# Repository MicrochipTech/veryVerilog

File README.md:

# veryVerilog

veryVerilog enables an easy way to program PICs from family 
- **PIC16F131xy**
- **PIC16F132xy**
- **PIC16F180xy**
- **PIC18FxyQ35**

over a Web Browser without the need to install any software using a PIC as a USB HiD device. 

The project is based on 3 parts:
- USB-HID PCB (hardware)
- USB-HID Hex File (firmware)
- Web Page to flash Hex files a PIC device attached to the hardware

The PCB looks like this and is based on a [**PIC16F1455**](https://www.microchip.com/en-us/product/pic16f1455) .

The [**PIC16F1455**](https://www.microchip.com/en-us/product/pic16f1455) needs a [**custom firmware**](/firmware/hex/U1_PIC16F1455_v1.20.hex) to perform as ICSP programmer.

The IC on the left-hand side is the [**PIC16F1455**](https://www.microchip.com/en-us/product/pic16f1455)-I/P and IC on the right-hand side is the miniFPGA ([**PIC16F13145**](https://www.microchip.com/en-us/product/pic16f13145)-I/P) to be programmed.

# Program a PIC in 4 Steps

It is that easy:

## 1. Insert the Hardware

Plug the miniFPGA dongle in your computer.

## 2. Click the Web Page

Open the Web Page: [https://microchiptech.github.io/veryVerilog](https://microchiptech.github.io/veryVerilog/).

You will see the veryVerilog Web Page:

## 3. Connect to Programmer

Click the button "Connect to Programmer" and select the miniFPGA device:

If you have multiple programmers connected, click "identify Programmer" and the LEDs of the connected board will blink for about 2 seconds.

The device is recognized and the Web Page displays information about the connected PIC and the identification of the program already flashed on the device (User Id)

## 4. Drag and Drop

Drag a HEX file on the *"Drag and Drop"* area and the program will be transfered automatically to the PIC.

Alternatively, you can click the **"Browse for HEX file"** button to select a HEX file from your file system. This is particularly useful when working with IDEs where you can copy and paste file paths.

Have fun!

## Additional Features

### Reset Target Device

After connecting to the programmer, a **"Reset Target"** button becomes available. Clicking this button will reset the target PIC.

### Device Detection

When you connect to a programmer:
- If the device is **recognized**, the web page displays the PIC model name (e.g., "PIC16F13145") and its User ID
- If the device is **not recognized** or reads an invalid ID (like 0x0000), the page will display: **"Unknown PIC with DEVID 0x[hex_value]"** along with the actual device ID that was read

This helps in debugging connectivity issues or identifying when an unsupported PIC is connected.

**Tip:** Click on the **UserId** display to open a detailed information window showing:
- **MCU Parameters** - Device ID, Revision ID, Memory sizes (ERSIZ, WLSIZ, URSIZ, EESIZ), Program Counter size (PCNT), and other device-specific information
- **Programmer Parameters** - Hardware UART baud rate and other programmer settings

### Reading Memory Regions

After connecting to the programmer, you can read the entire contents of the target PIC device:

1. Click the **Settings** dropdown (split button next to "Identify Programmer")
2. Select **"Read Device"** from the menu
3. The device memory will be read and automatically displayed in a modal window

The memory viewer organizes data into collapsible sections:
- **Program Flash** - The main program memory (displayed in rows of 16 words)
- **EEPROM** - Data EEPROM memory (if available on the device, displayed in rows of 8 bytes)
- **UserId** - User ID locations (displayed in rows of 4 words)
- **Config Words** - Configuration bits

You can also access previously read memory using the **"Show Memory"** option without reading the device again. This is useful for comparing data or reviewing what was last read from the device.

### Programming Settings

The **Settings** dropdown provides options to customize which memory regions are programmed and whether verification is performed:

**Default Behavior:**
- All memory regions are programmed: **Program** (Flash), **EEPROM**, **UserId**, and **Config Bits**
- After programming, the code is automatically **verified** to ensure it was written correctly

**Customizing Memory Regions:**

Click the **Settings** dropdown to access programming options. You can selectively choose which memory regions to program by checking/unchecking:
- **Program** - Main program flash memory
- **EEPROM** - Data EEPROM memory (if available on the device)
- **UserId** - User ID locations
- **Config Bits** - Configuration bits

**Verification:**
- The **Verify** option (enabled by default) checks that the programmed memory matches the expected values
- This ensures programming integrity but may increase programming time slightly
- You can disable verification if faster programming is needed, though this is not recommended

### Serial Terminal

The veryVerilog web page includes a built-in **Serial Terminal** for communicating directly with the target PIC over a serial (UART) connection.

#### Opening the Serial Terminal

Click the **"Serial Terminal"** tab to open the terminal window:

#### Connecting to a Serial Port

Click the **"Connect"** button and a browser popup will appear listing the available serial ports on your computer. Select the desired port (e.g., the miniFPGA board) and click **Connect**:

Once connected, the status indicator turns green and the terminal displays a confirmation message with a timestamp:

#### Sending Data

Type a command in the input field at the bottom of the terminal and press **Enter** or click the **"Send"** button. Use the **line ending** dropdown (default: **CR+LF**) to choose the line termination characters appended to each message.

#### Terminal Controls

The toolbar at the top of the terminal provides the following controls:

| Button | Description |
|--------|-------------|
| **Connect** / **Disconnect** | Connect to or disconnect from a serial port. The button label changes depending on the connection state. |
| **Pause** | Pause the terminal output. Incoming data is still received but the display stops scrolling. Click again to resume. |
| **Graph** | Open a graphing view to plot numeric data received from the serial port in real time (see [Graph Mode](#graph-mode) below). |
| **X** (Clear Terminal) | Clear all text currently displayed in the terminal window. |
| **Hide Terminal** | Collapse the serial terminal panel to free up screen space. Click the **"Serial Terminal"** tab again to reopen it. |

#### Graph Mode

Click the **"Graph"** button to switch the terminal into a real-time plotting view. The graph plots numeric data received over the serial port in **CSV format** — each line of text represents one data point in time, with comma-separated values mapping to individual channels.

**Expected data format:**

The PIC should send an optional **header line** followed by **numeric data lines**, all in CSV format terminated by a newline:

```
header1,header2,header3\n   ← optional: names for each channel
value1,value2,value3\n      ← numeric data (one sample per line)
value1,value2,value3\n
...
```

The first non-numeric line received is used as the **channel names** displayed in the graph legend. If no header is sent, channels are automatically named `Ch1`, `Ch2`, etc.

> **Tip:** Always send a header line at PIC startup to get meaningful trace names. Without it, UART noise or partial bytes at connection time may produce garbled labels.

**Example — single channel** (e.g., ADC reading):
```
ADC
512
523
531
548
```

**Example — multiple channels** (e.g., temperature and humidity sensors):
```
Temperature,Humidity
23.5,65.2
23.6,64.8
23.7,65.0
23.8,64.5
```

**Example C code** to send plottable data from a PIC:
```c
// Send header once at startup
printf("ADC,Temperature\r\n");

// Then send data periodically
while (1) {
    printf("%d,%d\r\n", adc_value, temperature);
    __delay_ms(100);
}
```

Each comma-separated value is plotted as a separate trace on the graph, allowing you to monitor multiple signals simultaneously. The example below shows two channels — one counting up from 0 to 10 and the other counting down from 10 to 0 — plotted in real time:

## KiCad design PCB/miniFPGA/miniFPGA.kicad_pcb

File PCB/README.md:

# v3.0 PCB Readme

## Overview
This document provides essential information regarding the v3.0 PCB (Printed Circuit Board) design, including features, specifications, and usage instructions.

## Features
- **Compact Design**: The v3.0 PCB is designed to be space-efficient while maintaining functionality.
- **Power Management**: Improved power distribution for optimal performance and reduced heat generation.

## Specifications
- **Dimensions**: 57.4mm x 24.89mm
- **Layer Count**: 2 layers
- **Material**: FR-4
- **Operating Voltage**: 5V (from USB A)
- **Current Rating**: 100mA without external application

## Schematic
Refer to the attached schematic diagram for detailed connections and component placements.

## Assembly Instructions
1. **Component Placement**: Follow the provided schematic for correct component placement. Use IBOM from miniFPGA/bom/miniFPGA?ibom.html
2. **Soldering**: Use appropriate soldering techniques to ensure reliable connections.
3. **Testing**: After assembly, U2 LEDs will shor a running light effect.

## Usage
- Connect the PCB USB-A port. Use the [web programmer application](https://microchiptech.github.io/veryVerilog)
- The lectures are on [Microchip try platform](https://try.microchip.com/training/logic-circuit-design-101)     

## Troubleshooting
- **No Power**: Check power supply connections and ensure the correct voltage is applied.
- **Component Failure**: Inspect for soldering issues or damaged components.

## License
This project is licensed under the MIT License - see the LICENSE file for details.

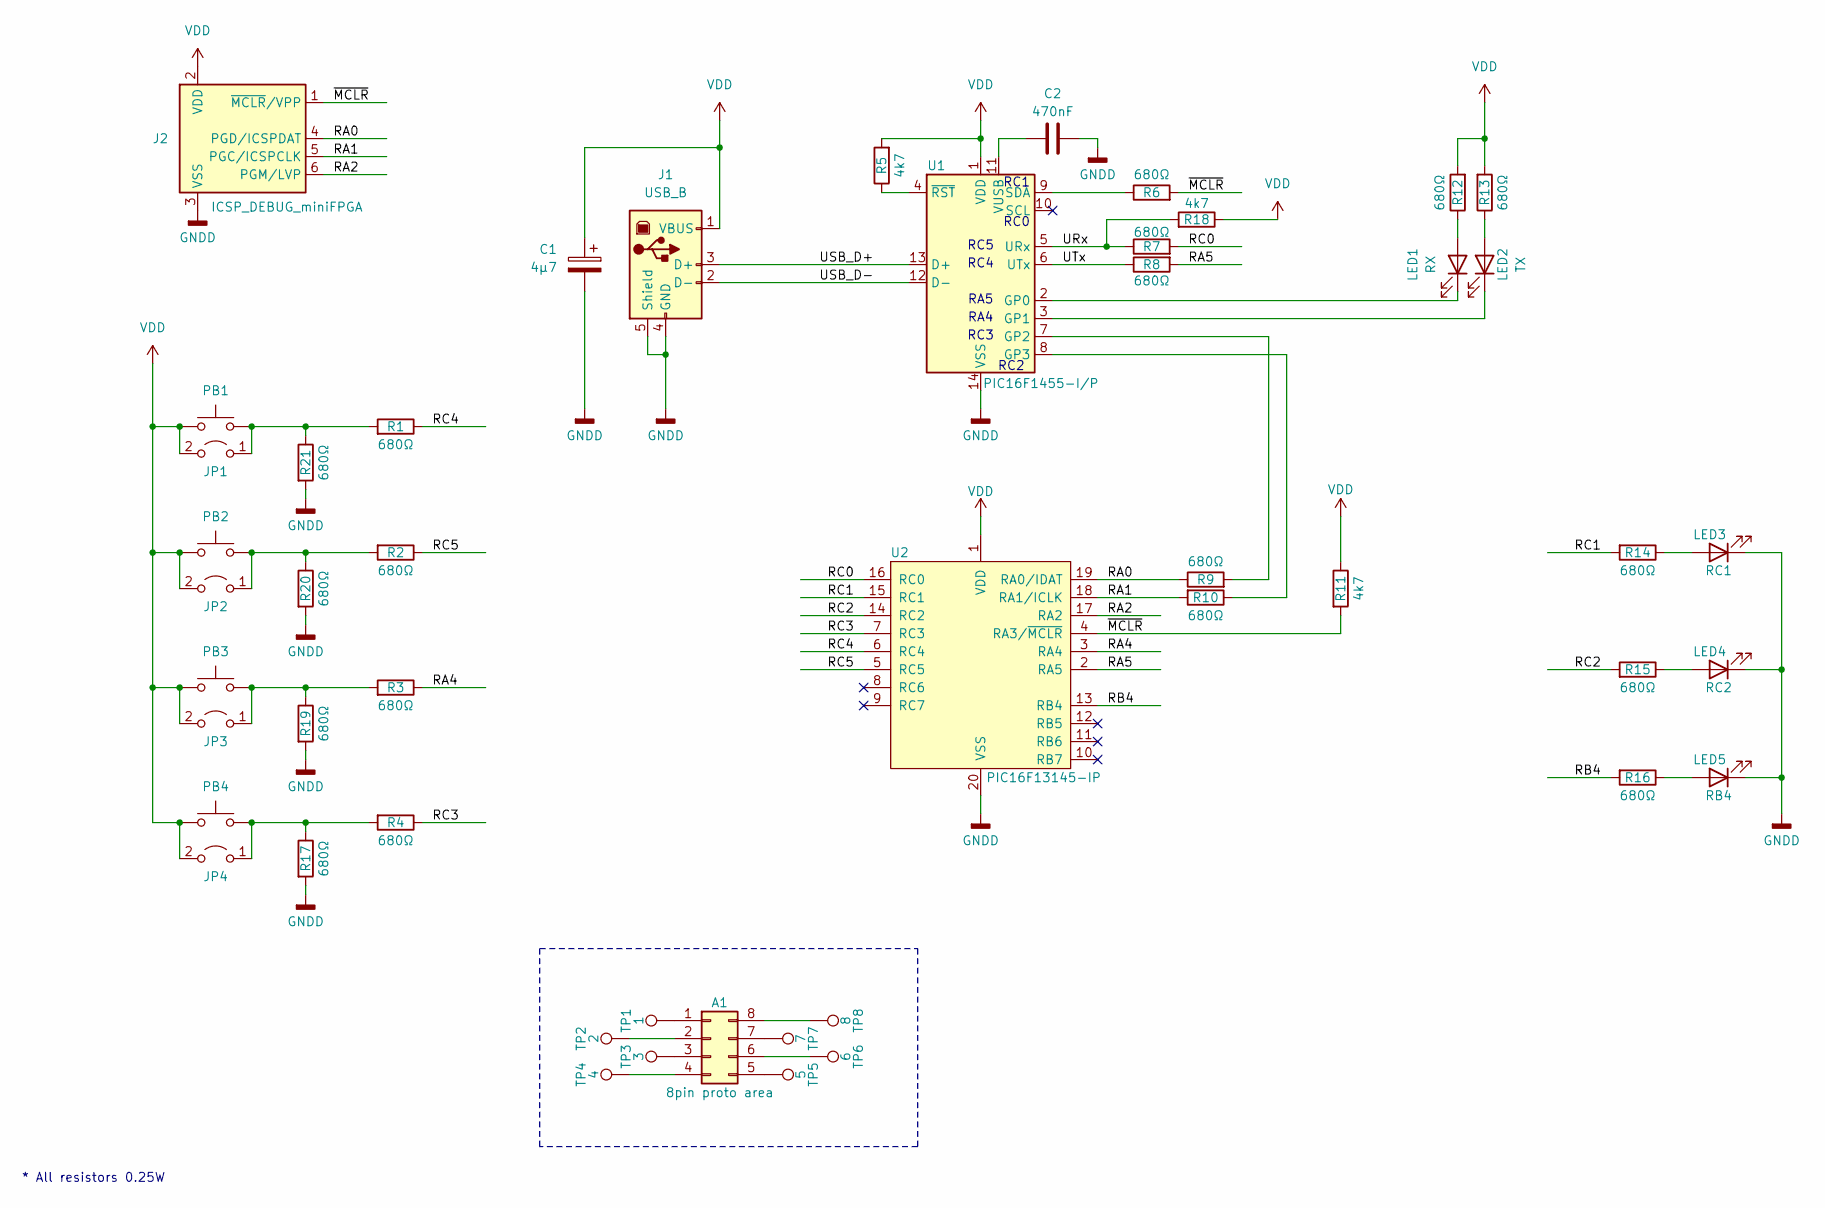
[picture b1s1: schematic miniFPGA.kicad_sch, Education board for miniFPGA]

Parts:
A1: 8pin proto area; 8pin_proto
C1: 4µ7; CP_Radial_D4.0mm_P2.00mm
C2: 470nF; C_Rect_L4.6mm_W2.0mm_P2.50mm_MKS02_FKP02
J1: USB_B; USB_A_CNCTech_1001-011-01101_Horizontal
J2: ICSP_DEBUG_miniFPGA; PinHeader_1x06_P2.54mm_Horizontal
JP1: RC4; PinHeader_1x02_P2.54mm_Vertical
JP2: RC5; PinHeader_1x02_P2.54mm_Vertical
JP3: RA4; PinHeader_1x02_P2.54mm_Vertical
JP4: RC3; PinHeader_1x02_P2.54mm_Vertical
LED1: RX; LED_D3.0mm
LED2: TX; LED_D3.0mm
LED3: RC1; LED_D3.0mm
LED4: RC2; LED_D3.0mm
LED5: RB4; LED_D3.0mm
PB1: RC4; SW_PUSH_6mm_H5mm
PB2: RC5; SW_PUSH_6mm_H5mm
PB3: RA4; SW_PUSH_6mm_H5mm
PB4: RC3; SW_PUSH_6mm_H5mm
R1, R2, R3, R4, R6, R7, R8, R9, R10, R12, R13, R14, R15, R16, R17, R19, R20, R21: 680Ω; R_Axial_L3.6mm_D1.6mm_P1.90mm_Vertical
R5, R11, R18: 4k7; R_Axial_DIN0204_L3.6mm_D1.6mm_P5.08mm_Horizontal
TP1: 1; TestPoint_Pad_1.5x1.5mm
TP2: 2; TestPoint_Pad_D1.5mm
TP3: 3; TestPoint_Pad_D1.5mm
TP4: 4; TestPoint_Pad_D1.5mm
TP5: 5; TestPoint_Pad_D1.5mm
TP6: 6; TestPoint_Pad_D1.5mm
TP7: 7; TestPoint_Pad_D1.5mm
TP8: 8; TestPoint_Pad_D1.5mm
U1: PIC16F1455-I/P; DIP-14_W7.62mm
U2: PIC16F13145-IP; DIP-20_W7.62mm

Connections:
/RA0: J2.4 (PGD/ICSPDAT), R9.1, U2.19 (RA0/IDAT)
/RA1: J2.5 (PGC/ICSPCLK), R10.2, U2.18 (RA1/ICLK)
/RA2: J2.6 (PGM/LVP), U2.17 (RA2)
/RA4: R3.1, U2.3 (RA4)
/RA5: R8.2, U2.2 (RA5)
/RB4: R16.2, U2.13 (RB4)
/RC0: R7.2, U2.16 (RC0)
/RC1: R14.2, U2.15 (RC1)
/RC2: R15.2, U2.14 (RC2)
/RC3: R4.1, U2.7 (RC3)
/RC4: R1.1, U2.6 (RC4)
/RC5: R2.1, U2.5 (RC5)
/URx: R7.1, R18.2, U1.5 (URx)
/USB_D+: J1.3 (D+), U1.13 (D+)
/USB_D-: J1.2 (D-), U1.12 (D-)
/UTx: R8.1, U1.6 (UTx)
/~MCLR: J2.1 (~MCLR/VPP), R6.2, R11.2, U2.4 (RA3/~MCLR)
GNDD: C1.2, C2.2, J1.4 (GND), J1.5 (Shield), J2.3 (VSS), LED3.1 (K), LED4.1 (K), LED5.1 (K), R17.2, R19.2, R20.2, R21.2, U1.14 (VSS), U2.20 (VSS)
unnamed: A1.1, TP1.1
unnamed: A1.2, TP2.1
unnamed: A1.3, TP3.1
unnamed: A1.4, TP4.1
unnamed: A1.5, TP5.1
unnamed: A1.6, TP6.1
unnamed: A1.7, TP7.1
unnamed: A1.8, TP8.1
unnamed: JP1.1 (A), PB1.1, R1.2, R21.1
unnamed: JP2.1 (A), PB2.1, R2.2, R20.1
unnamed: JP3.1 (A), PB3.1, R3.2, R19.1
unnamed: JP4.1 (A), PB4.1, R4.2, R17.1
unnamed: LED1.2 (A), R12.1
unnamed: LED1.1 (K), U1.2 (GP0)
unnamed: LED2.2 (A), R13.1
unnamed: LED2.1 (K), U1.3 (GP1)
unnamed: LED3.2 (A), R14.1
unnamed: LED4.2 (A), R15.1
unnamed: LED5.2 (A), R16.1
unnamed: R9.2, U1.7 (GP2)
unnamed: R10.1, U1.8 (GP3)
unnamed: R6.1, U1.9 (SDA)
unnamed: C2.1, U1.11 (VUSB)
unnamed: R5.1, U1.4 (~RST)
VDD: C1.1, J1.1 (VBUS), J2.2 (VDD), JP1.2 (B), JP2.2 (B), JP3.2 (B), JP4.2 (B), PB1.2, PB2.2, PB3.2, PB4.2, R5.2, R11.1, R12.2, R13.2, R18.1, U1.1 (VDD), U2.1 (VDD)

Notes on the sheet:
RC3
RC1
RC0
RA5
RC4
RA4
* All resistors 0.25W
RC2
RC5

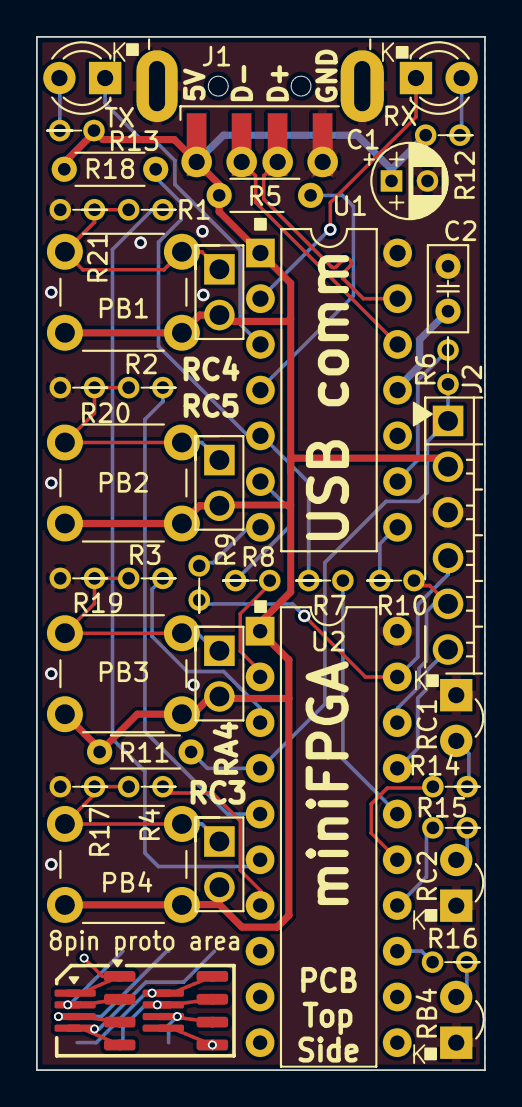
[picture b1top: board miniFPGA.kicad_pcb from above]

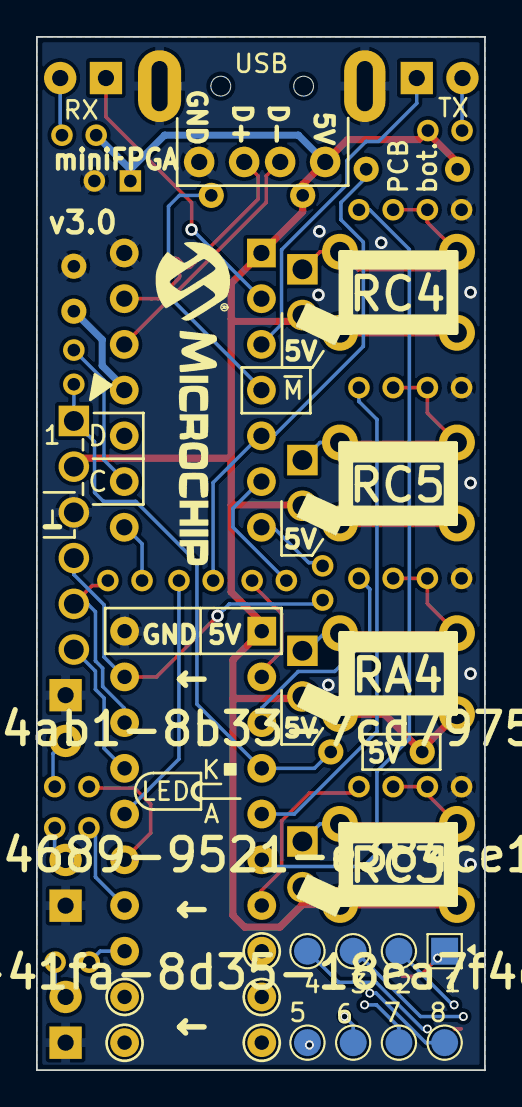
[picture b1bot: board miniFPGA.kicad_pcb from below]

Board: 2 copper layers, 24.9 x 57.4 mm, 49 parts (8 on the bottom side), 43 nets.

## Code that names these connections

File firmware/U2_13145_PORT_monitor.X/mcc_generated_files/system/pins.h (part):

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// get/set IO_RA0 aliases
#define IO_RA0_TRIS                 TRISAbits.TRISA0
#define IO_RA0_LAT                  LATAbits.LATA0
#define IO_RA0_PORT                 PORTAbits.RA0
#define IO_RA0_WPU                  WPUAbits.WPUA0
#define IO_RA0_OD                   ODCONAbits.ODCA0
#define IO_RA0_ANS                  ANSELAbits.ANSA0
#define IO_RA0_SetHigh()            do { LATAbits.LATA0 = 1; } while(0)
#define IO_RA0_SetLow()             do { LATAbits.LATA0 = 0; } while(0)
#define IO_RA0_Toggle()             do { LATAbits.LATA0 = ~LATAbits.LATA0; } while(0)
#define IO_RA0_GetValue()           PORTAbits.RA0
#define IO_RA0_SetDigitalInput()    do { TRISAbits.TRISA0 = 1; } while(0)
#define IO_RA0_SetDigitalOutput()   do { TRISAbits.TRISA0 = 0; } while(0)
#define IO_RA0_SetPullup()          do { WPUAbits.WPUA0 = 1; } while(0)
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// get/set IO_RA1 aliases
#define IO_RA1_TRIS                 TRISAbits.TRISA1
#define IO_RA1_LAT                  LATAbits.LATA1
#define IO_RA1_PORT                 PORTAbits.RA1
#define IO_RA1_WPU                  WPUAbits.WPUA1
#define IO_RA1_OD                   ODCONAbits.ODCA1
#define IO_RA1_ANS                  ANSELAbits.ANSA1
#define IO_RA1_SetHigh()            do { LATAbits.LATA1 = 1; } while(0)
#define IO_RA1_SetLow()             do { LATAbits.LATA1 = 0; } while(0)
#define IO_RA1_Toggle()             do { LATAbits.LATA1 = ~LATAbits.LATA1; } while(0)
#define IO_RA1_GetValue()           PORTAbits.RA1
#define IO_RA1_SetDigitalInput()    do { TRISAbits.TRISA1 = 1; } while(0)
#define IO_RA1_SetDigitalOutput()   do { TRISAbits.TRISA1 = 0; } while(0)
#define IO_RA1_SetPullup()          do { WPUAbits.WPUA1 = 1; } while(0)
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// get/set IO_RA2 aliases
#define IO_RA2_TRIS                 TRISAbits.TRISA2
#define IO_RA2_LAT                  LATAbits.LATA2
#define IO_RA2_PORT                 PORTAbits.RA2
#define IO_RA2_WPU                  WPUAbits.WPUA2
#define IO_RA2_OD                   ODCONAbits.ODCA2
#define IO_RA2_ANS                  ANSELAbits.ANSA2
#define IO_RA2_SetHigh()            do { LATAbits.LATA2 = 1; } while(0)
#define IO_RA2_SetLow()             do { LATAbits.LATA2 = 0; } while(0)
#define IO_RA2_Toggle()             do { LATAbits.LATA2 = ~LATAbits.LATA2; } while(0)
#define IO_RA2_GetValue()           PORTAbits.RA2
#define IO_RA2_SetDigitalInput()    do { TRISAbits.TRISA2 = 1; } while(0)
#define IO_RA2_SetDigitalOutput()   do { TRISAbits.TRISA2 = 0; } while(0)
#define IO_RA2_SetPullup()          do { WPUAbits.WPUA2 = 1; } while(0)
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// get/set IO_RA4 aliases
#define IO_RA4_TRIS                 TRISAbits.TRISA4
#define IO_RA4_LAT                  LATAbits.LATA4
#define IO_RA4_PORT                 PORTAbits.RA4
#define IO_RA4_WPU                  WPUAbits.WPUA4
#define IO_RA4_OD                   ODCONAbits.ODCA4
#define IO_RA4_ANS                  ANSELAbits.ANSA4
#define IO_RA4_SetHigh()            do { LATAbits.LATA4 = 1; } while(0)
#define IO_RA4_SetLow()             do { LATAbits.LATA4 = 0; } while(0)
#define IO_RA4_Toggle()             do { LATAbits.LATA4 = ~LATAbits.LATA4; } while(0)
#define IO_RA4_GetValue()           PORTAbits.RA4
#define IO_RA4_SetDigitalInput()    do { TRISAbits.TRISA4 = 1; } while(0)
#define IO_RA4_SetDigitalOutput()   do { TRISAbits.TRISA4 = 0; } while(0)
#define IO_RA4_SetPullup()          do { WPUAbits.WPUA4 = 1; } while(0)
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// get/set IO_RA5 aliases
#define IO_RA5_TRIS                 TRISAbits.TRISA5
#define IO_RA5_LAT                  LATAbits.LATA5
#define IO_RA5_PORT                 PORTAbits.RA5
#define IO_RA5_WPU                  WPUAbits.WPUA5
#define IO_RA5_OD                   ODCONAbits.ODCA5
#define IO_RA5_ANS                  ANSELAbits.ANSA5
#define IO_RA5_SetHigh()            do { LATAbits.LATA5 = 1; } while(0)
#define IO_RA5_SetLow()             do { LATAbits.LATA5 = 0; } while(0)
#define IO_RA5_Toggle()             do { LATAbits.LATA5 = ~LATAbits.LATA5; } while(0)
#define IO_RA5_GetValue()           PORTAbits.RA5
#define IO_RA5_SetDigitalInput()    do { TRISAbits.TRISA5 = 1; } while(0)
#define IO_RA5_SetDigitalOutput()   do { TRISAbits.TRISA5 = 0; } while(0)
#define IO_RA5_SetPullup()          do { WPUAbits.WPUA5 = 1; } while(0)
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// get/set IO_RB4 aliases
#define IO_RB4_TRIS                 TRISBbits.TRISB4
#define IO_RB4_LAT                  LATBbits.LATB4
#define IO_RB4_PORT                 PORTBbits.RB4
#define IO_RB4_WPU                  WPUBbits.WPUB4
#define IO_RB4_OD                   ODCONBbits.ODCB4
#define IO_RB4_ANS                  ANSELBbits.ANSB4
#define IO_RB4_SetHigh()            do { LATBbits.LATB4 = 1; } while(0)
#define IO_RB4_SetLow()             do { LATBbits.LATB4 = 0; } while(0)
#define IO_RB4_Toggle()             do { LATBbits.LATB4 = ~LATBbits.LATB4; } while(0)
#define IO_RB4_GetValue()           PORTBbits.RB4
#define IO_RB4_SetDigitalInput()    do { TRISBbits.TRISB4 = 1; } while(0)
#define IO_RB4_SetDigitalOutput()   do { TRISBbits.TRISB4 = 0; } while(0)
#define IO_RB4_SetPullup()          do { WPUBbits.WPUB4 = 1; } while(0)
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// get/set IO_RC0 aliases
#define IO_RC0_TRIS                 TRISCbits.TRISC0
#define IO_RC0_LAT                  LATCbits.LATC0
#define IO_RC0_PORT                 PORTCbits.RC0
#define IO_RC0_WPU                  WPUCbits.WPUC0
#define IO_RC0_OD                   ODCONCbits.ODCC0
#define IO_RC0_ANS                  ANSELCbits.ANSC0
#define IO_RC0_SetHigh()            do { LATCbits.LATC0 = 1; } while(0)
#define IO_RC0_SetLow()             do { LATCbits.LATC0 = 0; } while(0)
#define IO_RC0_Toggle()             do { LATCbits.LATC0 = ~LATCbits.LATC0; } while(0)
#define IO_RC0_GetValue()           PORTCbits.RC0
#define IO_RC0_SetDigitalInput()    do { TRISCbits.TRISC0 = 1; } while(0)
#define IO_RC0_SetDigitalOutput()   do { TRISCbits.TRISC0 = 0; } while(0)
#define IO_RC0_SetPullup()          do { WPUCbits.WPUC0 = 1; } while(0)
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// get/set IO_RC1 aliases
#define IO_RC1_TRIS                 TRISCbits.TRISC1
#define IO_RC1_LAT                  LATCbits.LATC1
#define IO_RC1_PORT                 PORTCbits.RC1
#define IO_RC1_WPU                  WPUCbits.WPUC1
#define IO_RC1_OD                   ODCONCbits.ODCC1
#define IO_RC1_ANS                  ANSELCbits.ANSC1
#define IO_RC1_SetHigh()            do { LATCbits.LATC1 = 1; } while(0)
#define IO_RC1_SetLow()             do { LATCbits.LATC1 = 0; } while(0)
#define IO_RC1_Toggle()             do { LATCbits.LATC1 = ~LATCbits.LATC1; } while(0)
#define IO_RC1_GetValue()           PORTCbits.RC1
#define IO_RC1_SetDigitalInput()    do { TRISCbits.TRISC1 = 1; } while(0)
#define IO_RC1_SetDigitalOutput()   do { TRISCbits.TRISC1 = 0; } while(0)
#define IO_RC1_SetPullup()          do { WPUCbits.WPUC1 = 1; } while(0)
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// get/set IO_RC2 aliases
#define IO_RC2_TRIS                 TRISCbits.TRISC2
#define IO_RC2_LAT                  LATCbits.LATC2
#define IO_RC2_PORT                 PORTCbits.RC2
#define IO_RC2_WPU                  WPUCbits.WPUC2
#define IO_RC2_OD                   ODCONCbits.ODCC2
#define IO_RC2_ANS                  ANSELCbits.ANSC2
#define IO_RC2_SetHigh()            do { LATCbits.LATC2 = 1; } while(0)
#define IO_RC2_SetLow()             do { LATCbits.LATC2 = 0; } while(0)
#define IO_RC2_Toggle()             do { LATCbits.LATC2 = ~LATCbits.LATC2; } while(0)
#define IO_RC2_GetValue()           PORTCbits.RC2
#define IO_RC2_SetDigitalInput()    do { TRISCbits.TRISC2 = 1; } while(0)
#define IO_RC2_SetDigitalOutput()   do { TRISCbits.TRISC2 = 0; } while(0)
#define IO_RC2_SetPullup()          do { WPUCbits.WPUC2 = 1; } while(0)
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// get/set IO_RC3 aliases
#define IO_RC3_TRIS                 TRISCbits.TRISC3
#define IO_RC3_LAT                  LATCbits.LATC3
#define IO_RC3_PORT                 PORTCbits.RC3
#define IO_RC3_WPU                  WPUCbits.WPUC3
#define IO_RC3_OD                   ODCONCbits.ODCC3
#define IO_RC3_ANS                  ANSELCbits.ANSC3
#define IO_RC3_SetHigh()            do { LATCbits.LATC3 = 1; } while(0)
#define IO_RC3_SetLow()             do { LATCbits.LATC3 = 0; } while(0)
#define IO_RC3_Toggle()             do { LATCbits.LATC3 = ~LATCbits.LATC3; } while(0)
#define IO_RC3_GetValue()           PORTCbits.RC3
#define IO_RC3_SetDigitalInput()    do { TRISCbits.TRISC3 = 1; } while(0)
#define IO_RC3_SetDigitalOutput()   do { TRISCbits.TRISC3 = 0; } while(0)
#define IO_RC3_SetPullup()          do { WPUCbits.WPUC3 = 1; } while(0)
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// get/set IO_RC4 aliases
#define IO_RC4_TRIS                 TRISCbits.TRISC4
#define IO_RC4_LAT                  LATCbits.LATC4
#define IO_RC4_PORT                 PORTCbits.RC4
#define IO_RC4_WPU                  WPUCbits.WPUC4
#define IO_RC4_OD                   ODCONCbits.ODCC4
#define IO_RC4_ANS                  ANSELCbits.ANSC4
#define IO_RC4_SetHigh()            do { LATCbits.LATC4 = 1; } while(0)
#define IO_RC4_SetLow()             do { LATCbits.LATC4 = 0; } while(0)
#define IO_RC4_Toggle()             do { LATCbits.LATC4 = ~LATCbits.LATC4; } while(0)
#define IO_RC4_GetValue()           PORTCbits.RC4
#define IO_RC4_SetDigitalInput()    do { TRISCbits.TRISC4 = 1; } while(0)
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
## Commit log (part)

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2024-12-17 update gitignore
2024-12-17 adding files
2024-12-17 enhancing readme
2024-12-17 update images
2024-12-17 adding gh-pages
2024-12-17 Feat include files (#1)
    * update gitignore
    * adding files
    * enhancing readme
    * adding gh-pages
    ---------
2024-12-17 adding github action
2024-12-17 saving files to gh-pages
2024-12-17 git commit -m "Add .nojekyll to disable Jekyll processing"
2024-12-17 update web page link
2024-12-17 exit LVP before disconnect
2024-12-17 adapted read and show memory
2024-12-17 including LVPExit where it was missing
2024-12-17 including verify
2024-12-18 including tooltips
2024-12-18 included variable verify. It is checked but not yet implemented
2024-12-18 Feat enhance web interface (#2)
    * exit LVP before disconnect
    * adapted read and show memory
    * including verify memory variable
    * including tooltips
    ---------
2024-12-18 Deploy www folder to gh-pages
2024-12-18 PCB v3 image, more details in readme
2024-12-18 lessons' placeholders are now hidden
2024-12-19 lessons' placeholders are now hidden (#11)
2024-12-19 sync to gh-pages
2024-12-19 hide lesson image from readme
2024-12-19 update firmware hex version
2024-12-19 update MPLabX U1 and U2 projects
2024-12-19 instruction to deploy gh-pages
2024-12-19 Fix u1 and u2 firmware missing (#12)
    * update firmware hex version
    * update MPLabX U1 and U2 projects
    * hide lesson image from readme
    * instruction to deploy gh-pages
    ---------
2024-12-19 PCB v3 image, more details in readme (#10)
    * PCB v3 image, more details in readme
    * Update README.md
    ---------
2025-01-02 fix handling no EEPROM
2025-01-02 fix handling no EEPROM (#18)
2025-01-02 setting verify flag in class
2025-03-03 PCB v3 build instructions
2025-03-25 Add version display to WEB ICSP Programmer interface
2025-03-25 Add version display to WEB ICSP Programmer interface (#21)
2025-03-26 handling disconnect event
2025-03-26 handling disconnect event (#23)
2025-03-26 splitting functions to read specific memory area
2025-03-28 verifiy flash after programming ok
2025-03-28 refactored pic classes
2025-03-29 verify implemented
2025-03-29 increasing version
2025-03-29 13 pic16f13145 partially programmed (#24)
    * setting verify flag in class
    * handling disconnect event (#23)
    * verify flash after programming
    * refactored pic classes
    * verify implemented
    * increasing version
2025-04-05 Add v3.0 PCB source files
2025-04-05 PCB sources for v3.0
2025-04-05 version 2 sources and gerbers
2025-04-05 PCB v3 sources gerbers and schematics for V3.0 PCB Closes #26
2025-04-05 Add readme to PCB Closes #27
2025-04-05 Add hyperlinks to relevant material Closes #30
2025-04-06 including image of PIC16F13145 connected
2025-04-06 including image of PIC16F13145 connected (#34)
    image of PIC16F13145 is included to the readme to reflect the default PIC connected
2025-04-06 change default size to 850px
2025-04-06 refactoring
2025-04-06 29 table misalignment (#35)
    * change default size to 850px
    * refactoring format
2025-04-29 version update
2025-04-29 position weblinks at the bottom
2025-04-29 Release v1.6 (#36)
    * version update
    * position weblinks at the bottom
    ---------
2026-02-10 Ignoring backups
2026-02-10 Ignoring PCB cache
2026-02-10 Gitignore for MPLABX
2026-02-10 Test FW
2026-02-10 Rename original DEMO to show it's functionality
2026-02-10 Input test FW v1.0
2026-03-20 PIC16F132×× support based on DS40002646A Fixes #45
2026-03-23 PCB v3 build instructions
    (cherry picked from commit 6fec380db9f3f9508b77bb5478fa1088c89183d5)
2026-03-23 3D rendering corrected in DOCS Fixes #37
2026-03-23 DCE / DTE clarification on RX/TX In schematics and PDF Fixes #41
2026-03-23 Apshu/issue50 (#51)
    * Gitignore for MPLABX
    * Test FW
    * Rename original DEMO to show it's functionality
    * Input test FW v1.0
    ---------
2026-03-23 3D rendering corrected in DOCS (#54)
    * PCB v3 build instructions
    (cherry picked from commit 6fec380db9f3f9508b77bb5478fa1088c89183d5)
    * 3D rendering corrected in DOCS
    Fixes #37
    ---------
2026-03-23 PIC16F132×× support based on DS40002646A (#53)
    Fixes #45
2026-03-23 fix version
2026-03-23 show message with unknown devID
2026-03-23 auto close on pic programmed
2026-03-23 add progress bar during operation
2026-03-23 adding authors
2026-03-23 added reset target
2026-03-23 adding browse hex functionality
2026-03-23 DCE / DTE clarification on RX/TX (#55)
    * PCB v3 build instructions
    (cherry picked from commit 6fec380db9f3f9508b77bb5478fa1088c89183d5)
    * 3D rendering corrected in DOCS
    Fixes #37
    * DCE / DTE clarification on RX/TX
    In schematics and PDF
2026-03-23 enhance readme
2026-03-24 BUGFIX: getHwBaudRate function now waits for answer
2026-03-24 BUGFIX: setHwBaudRate now waits for answer and takes data from first reply chunk
2026-03-24 New table for programmer parameter(s). Closes #49
2026-03-24 Cleaner UI Closes #58
2026-03-25 New table for programmer parameter(s). Closes #49 (#57)
    * BUGFIX: getHwBaudRate function now waits for answer
    * BUGFIX: setHwBaudRate now waits for answer and takes data from first reply chunk
    * New table for programmer parameter(s). Closes #49
    ---------
2026-03-25 changing names and links of authors
2026-03-25 fix load hex poping twice
2026-03-25 extendind jquery usage
2026-03-25 optmized modal to ModalManager
2026-03-25 hdding control buttons
2026-03-25 Update web v1.8 (#56)
    * fix version v1.8
    * show message with unknown devID
    * auto close on pic programmed
    * add progress bar during operation
    * adding authors
    * added reset target
2026-03-27 Revise supported PIC families in README
    Updated the list of supported PIC families in the README.
2026-03-27 fix kicad file
2026-03-27 fix kicad file (#62)
2026-03-27 sync to gh-pages v1.8
2026-03-27 prevent default behavior after closing window
2026-03-27 prevent default behavior after closing window (#64)
2026-03-27 sync to gh-pages v1.8.1
2026-06-10 adding serial terminal
2026-06-10 version 1.9
2026-06-11 include PIC18FXXQ35

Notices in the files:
firmware/U2_13145_PORT_monitor.X/mcc_generated_files/system/pins.h:
© [2026] Microchip Technology Inc. and its subsidiaries.
